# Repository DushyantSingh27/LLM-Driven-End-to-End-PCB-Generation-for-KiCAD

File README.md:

# LLM-Driven End-to-End PCB Generation for KiCad

Turn a natural-language circuit description into an **ERC-clean KiCad 9 schematic** and a **DRC-checked, routed PCB** — headless, no GUI step anywhere in the flow.

Design intent is guided by STMicroelectronics hardware design guidelines, with mentorship from ST engineers on layout practice. Manufacturability limits come from a fabricator's DFM specification. KiCad is treated as the single source of truth for every file format, and KiCad's own ERC and DRC verify the output independently of the code that produced it.

```
"STM32L476 talking to an LSM6DSM over SPI"
        │
        ├─ RAG (datasheets) + KiCad symbol resolver   →  authoritative pin table
        ├─ LLM                                        →  SKiDL (Python)
        ├─ SKiDL + ERC                                →  verified netlist
        ├─ placement + ST-style power wiring          →  native .kicad_sch
        ├─ footprints, rules, stitching, pours        →  .kicad_pcb
        ├─ Freerouting (DSN → SES)                    →  routed board
        └─ DRC + independent verifier                 →  report.json, exit 0 or 1
```

**Repo:** `https://github.com/DushyantSingh27/LLM-Driven-End-to-End-PCB-Generation-for-KiCAD`

---

## Table of contents

1. [What you get](#1-what-you-get)
2. [Requirements](#2-requirements)
3. [Install](#3-install)
4. [Configure](#4-configure--paths-you-must-change)
5. [Run the benchmark](#5-run-the-benchmark)
6. [Reading the output](#6-reading-the-output)
7. [Generating **your own** circuit](#7-generating-your-own-circuit)
8. [Troubleshooting](#8-troubleshooting)
9. [Known limits](#9-known-limits)
10. [Verified environment](#10-verified-environment)

---

## 1. What you get

The architecture rests on one separation, held throughout: **the language model decides what the circuit is; deterministic code decides what the files are.** The LLM never emits a coordinate, a trace width or a clearance. Conversely, no rule engine guesses which pin is a power pin — that comes from the netlist's own pin semantics.

Running the benchmark end-to-end reproduces this, on an STM32L476JGYxP (WLCSP-72) + LSM6DSM (LGA-14) SPI board:

| Result | Value |
|---|---|
| Components / nets / pads | 22 / 68 / 126 |
| ERC errors | **0** |
| Independent verifier | clean |
| Pads bound to nets | 126 / 126 |
| Courtyard violations | 0 |
| Copper clearance violations | **0** |
| Traces / vias after routing | 94 / 44 |
| Unconnected items | 10 *(see [§9](#9-known-limits) — this is a deliberate trade)* |
| Exit code | `1` (`INCOMPLETE`) |

### Phase 1 output — the generated schematic

Native `.kicad_sch`, opened directly in Eeschema. Power rails auto-wired in ST's drawing style: T-junctions where the stacks fit, net labels where the pin column is crowded.

### Phase 2 output — placement and routing

Constructive placement from real ball coordinates, then a force-directed legaliser; routed by Freerouting through the DSN/SES bridge.

The pipeline **reports failure honestly**. Exit code `0` means DRC-clean; `1` means something is unresolved and the report says exactly what. Do not treat a non-zero exit as "the tool is broken" — read `report.json`.

---

## 2. Requirements

| | |
|---|---|
| **OS** | Windows 10/11 with **WSL2** (Ubuntu 22.04). The split is required — see below. |
| **Python** | 3.10 (in WSL) — *and* KiCad's own bundled `python.exe` (on Windows) |
| **KiCad** | **9.0.8** on the Windows side |
| **Java** | A JRE on the Windows side, for Freerouting |
| **Freerouting** | `freerouting.jar` |
| **API key** | Anthropic, and/or NVIDIA NIM (has a free tier) |
| **Disk** | ~2 GB (Chroma index + sentence-transformers model) |

### Why two operating systems?

`pcbnew` is a SWIG binding into KiCad's C++ core. It **must** run under the same interpreter KiCad ships with. `pip install`-ing it into a Linux venv gives ABI mismatches that fail in confusing ways — segfaults, or worse, silently wrong numbers.

**The rule:**

- Anything that is **pure logic** (SKiDL, RAG, resolver, netlist parsing, schematic emit) → **WSL Python**
- Anything that **touches a board object** (placement, rules, zones, DSN/SES, DRC) → **KiCad's Windows `python.exe`**

Paths cross with `wslpath -w` going out, and `/mnt/c/...` coming back.

---

## 3. Install

### 3.1 WSL and Python

```bash
# From Windows PowerShell (once):
wsl --install -d Ubuntu-22.04
```

```bash
# Then, inside WSL:
sudo apt update
sudo apt install -y python3.10 python3.10-venv python3-pip git

cd ~
git clone https://github.com/DushyantSingh27/LLM-Driven-End-to-End-PCB-Generation-for-KiCAD.git LLM_Driven_Schematic_Gen
cd LLM_Driven_Schematic_Gen

python3 -m venv venv
source venv/bin/activate
python -V          # must print Python 3.10.x
```

> **The clone directory name matters.** Several scripts hardcode `~/LLM_Driven_Schematic_Gen`. Clone into exactly that name, or edit the paths in [§4](#4-configure--paths-you-must-change).

### 3.2 Python dependencies

```bash
pip install skidl==2.2.3
pip install anthropic==0.115.1
pip install openai==2.46.0
pip install pymupdf4llm==1.28.0 pymupdf-layout==1.28.0
pip install chromadb==1.5.9
pip install sentence-transformers==5.6.0
```

> **Do not substitute plain PyMuPDF for `pymupdf4llm`.** Plain extraction turns the STM32 ball-assignment tables into mojibake — which is precisely the data the model most needs. The failure does not appear until three stages later, as an invalid pin name.

### 3.3 KiCad 9

Install **KiCad 9.0.8** from [kicad.org](https://www.kicad.org) (Windows installer). Then verify it from WSL:

```bash
ls "/mnt/c/Program Files/KiCad/9.0/share/kicad/symbols/" | head
"/mnt/c/Program Files/KiCad/9.0/bin/python.exe" -c "import pcbnew; print(pcbnew.GetBuildVersion())"
# expect: 9.0.8
```

> ⚠️ **The install path contains a space.** Quote it *everywhere*. Unquoted, it fails silently in about half of all shell contexts.

If your KiCad lives elsewhere, override the symbol directory:

```bash
export KICAD_SYMBOL_DIR="/mnt/c/Path/To/KiCad/9.0/share/kicad/symbols"
```

### 3.4 Freerouting and Java

Install a JRE on the **Windows** side and place the jar somewhere stable, e.g. `C:\tools\freerouting\freerouting.jar`.

```bash
java -version    # confirm the JRE is reachable
```

`rag/routing.py` performs java/jar discovery and drives it headless:

```
java -jar freerouting.jar -de board.dsn -do board.ses
```

> Check which JRE version your Freerouting build requires. Recent releases track new JREs and fail on older ones with an error that does not mention Java.

### 3.5 API keys

```bash
export ANTHROPIC_API_KEY=sk-ant-...      # console.anthropic.com
export NVIDIA_API_KEY=nvapi-...          # build.nvidia.com  (only if PROVIDER="nvidia")
```

Add them to `~/.bashrc` so they survive a new shell.

> **A Claude Pro subscription is not API access.** The API bills separately.

---

## 4. Configure — paths you must change

These are hardcoded. Change them, or match them.

| File | Constant | Default | Action |
|---|---|---|---|
| `rag/pipeline.py` | `DEFAULT_OUTPUT_ROOT` | `/mnt/c/Users/Dushyant/Desktop/pcbgen_outputs` | **Must change** — or always pass `--output-root` |
| `rag/build_rag_v2.py` | `DATASHEET_DIR` | `~/LLM_Driven_Schematic_Gen/datasheets` | OK if you cloned to that name |
| `rag/build_rag_v2.py` | `CHROMA_DIR` | `~/LLM_Driven_Schematic_Gen/rag/chroma_db` | OK if you cloned to that name |
| `rag/build_rag_v2.py` | `COLLECTION` | `st_datasheets_v2` | Leave alone unless you keep multiple corpora |
| `rag/generate_spi_v2.py` | `PROVIDER` | `"anthropic"` | Set to the provider whose key you have |
| `rag/generate_spi_v2.py` | `MODEL` | `claude-sonnet-4-6` | Change to switch Anthropic model |
| `rag/generate_spi_v2.py` | `NVIDIA_MODEL` | `z-ai/glm-5.2` | Used when `PROVIDER` is NVIDIA |
| `rag/generate_spi_v2.py` | `OUTPUT_PY` | `rag/lsm6dsm_stm32l476_spi_v2.py` | Where the generated SKiDL is written |
| *(env)* | `KICAD_SYMBOL_DIR` | KiCad 9 default path | Set only if KiCad is installed elsewhere |

The output root must be a **Windows-visible** path (under `/mnt/c/...`), because Phase 2 runs under Windows Python and has to read what Phase 1 wrote.

---

## 5. Run the benchmark

### Step 1 — Build the RAG index *(once per datasheet set)*

Put component datasheet PDFs in `datasheets/`. The filename becomes the component key:

```
datasheets/STM32L476.pdf   →  component "STM32L476"
datasheets/LSM6DSM.pdf     →  component "LSM6DSM"
```

```bash
source ~/LLM_Driven_Schematic_Gen/venv/bin/activate
cd ~/LLM_Driven_Schematic_Gen/rag
python build_rag_v2.py
```

Extracts with `pymupdf4llm` (layout-aware markdown), splits on `#`/`##`/`###`, chunks at 1200 chars with 120 overlap, embeds, and writes a persistent Chroma collection to `rag/chroma_db`.

### Step 2 — Phase 1: prompt → verified schematic

```bash
python pipeline.py --name spi_auto --output-root /mnt/c/Users/<YOU>/Desktop/pcbgen_outputs
```

One command. It runs generation (LLM → SKiDL → ERC), then the serialiser (netlist → placement → ST-style power wiring → `.kicad_sch`), then verification.

```bash
# Re-run the serialiser on the last generated netlist, without paying for tokens:
python pipeline.py --name spi_auto --skip-generate
```

`--skip-generate` is the flag you will use most. Use it whenever you are debugging the serialiser rather than the model.

### Step 3 — Phase 2: netlist → routed board

Launch this with **KiCad's Windows Python**, not the venv:

```bash
RUN=/mnt/c/Users/<YOU>/Desktop/pcbgen_outputs/spi_auto

"/mnt/c/Program Files/KiCad/9.0/bin/python.exe" \
  "$(wslpath -w ~/LLM_Driven_Schematic_Gen/rag/layout_pipeline.py)" \
  "$(wslpath -w $RUN/spi_auto.net)" \
  "$(wslpath -w $RUN)"

echo "exit code: $?"     # 0 = DRC clean, 1 = incomplete
```

`layout_pipeline.py` takes exactly **two positional arguments**: the netlist path and the output directory. Both must be **Windows-style** paths.

---

## 6. Reading the output

`run_context.py` gives every run its own directory with structural uniqueness:

| Artifact | What it is |
|---|---|
| `board.kicad_pcb` | The board — open it in pcbnew |
| `board.dsn` | What was handed to the router |
| `board.ses` | What the router handed back |
| `drc.rpt` | KiCad's own DRC report |
| `router.log` | Freerouting's output, parsed for the unrouted count |
| `report.json` | **Start here.** Stage-by-stage results, not just a verdict. |

The console log is stage-numbered (`[L1/12] … [L12/12]`) and names anything it could not do rather than dropping it silently — e.g. `UNREACHABLE U1 pad H8 (/VDD_3V3)`.

---

## 7. Generating your own circuit

The benchmark is not special. To generate a different board:

### 7.1 Add the datasheets

```bash
cp MY_MCU.pdf MY_SENSOR.pdf ~/LLM_Driven_Schematic_Gen/datasheets/
cd ~/LLM_Driven_Schematic_Gen/rag
python build_rag_v2.py        # rebuild the index
```

### 7.2 Edit the spec in `rag/generate_spi_v2.py`

Three constants define the circuit:

```python
USER_TASK  = "..."     # the natural-language spec, e.g. "connect X to Y over I2C
                       #  with pull-ups, decouple every supply rail"
COMPONENTS = {...}     # part number → KiCad symbol/library mapping
RAG_QUERIES = [...]    # what to retrieve from the datasheets before prompting
```

`RAG_QUERIES` is the one people under-invest in. The model is only as grounded as what you retrieve. For a new part, query for the **ball/pin assignment table**, the **supply rail list**, and the **decoupling recommendations** at minimum.

There are worked examples in the repo for other topologies: `generate_i2c_circuit.py`, `generate_st_circuit.py`.

### 7.3 Run it

```bash
python pipeline.py --name my_board --output-root /mnt/c/Users/<YOU>/Desktop/pcbgen_outputs
```

then Phase 2 as in [§5 step 3](#step-3--phase-2-netlist--routed-board).

### 7.4 Expect to hit the generalisation gaps

Be aware before you start (details in [§9](#9-known-limits)):

- The placer contains **circuit-specific reference designators**. A different topology can trip them.
- Net names must match the pipeline's **contract** (`GND`, `VDD_3V3`, `VREF_PLUS`, …). A model that emits `VSS` or `VREF+` will break the power-wiring stage.
- Only **single-sided** placement is supported.

---

## 8. Troubleshooting

**`ImportError: No module named pcbnew`**
You ran Phase 2 with the venv Python. Use KiCad's `python.exe`.

**Design rules look wrong / clearance numbers don't match what you set**
KiCad 9 stores netclass **definitions** in the `.kicad_pro` project file, not the `.kicad_pcb`, and `SaveBoard` will not overwrite an existing project file. A stale `.kicad_pro` silently overrides your computed rules and invalidates every measurement taken afterwards. `save_board` clears them — but if you are writing your own stage, delete the project file before saving.

**Python exits with no traceback during the pour stage**
`ZONE_FILLER` hard-crashes at the C++ level on an in-memory board. `BuildConnectivity()` does not help. There is a deliberate **save/reload seam** before pouring; do not remove it.

**Netclasses vanish after a save/reload**
Expected — the definitions live in the project file. This is why DSN clearance inflation is done **in memory** and reverted immediately, rather than via a round-trip.

**A shell command "does nothing"**
You did not quote `"/mnt/c/Program Files/KiCad/9.0/..."`.

**The router succeeds but KiCad's DRC rejects the board**
DSN carries copper-to-copper clearance; it does **not** carry KiCad's hole-to-copper rule. The exported clearance is inflated so one implies the other:

```
c_router = max(c_copper, c_hole + r_hole − r_via) = 0.1250 mm
```

**Invalid pin names in the generated SKiDL**
Your RAG index is probably built from mangled extraction. Confirm `pymupdf4llm` is installed (not plain PyMuPDF) and rebuild.

---

## 9. Known limits

Stated plainly, because a pipeline that oversells itself moves error discovery to the fab.

**10 unconnected items — a measured trade, not a bug.**
All ten are WLCSP-72 inner-ball escape routes. At 0.4 mm ball pitch the keep-out ring leaves no legal channel for a through-via to reach U1's inner balls. The clearance choice was measured, not guessed:

| Router clearance | Unrouted | Hole violations |
|---|---|---|
| 0.09 mm | 6 | **14** |
| **0.1250 mm** | **10** | **0** |

The 0.09 mm board connects four more nets and is **not manufacturable**. The pipeline takes the manufacturable board. Closing the remaining ten is a *stackup* decision — microvias or more layers — not a router tuning problem.

**No intentional trace widths.** `m_TrackMinWidth` is a DRC minimum, not the width the router uses. Netclasses with real per-class widths are not implemented yet, so trace widths are the DSN default.

**Single-sided placement only.** The placer has no concept of a bottom side.

**Circuit-specific hardcodes in placement.** Some reference designators are baked in.

**No generation-contract normalisation.** `VSS`/`GND`, `VDD`/`VDD_3V3`, `VREF+`/`VREF_PLUS`, `100n`/`100nF` are not yet unified.

**Silkscreen placement not implemented.** 10 silkscreen warnings are deferred; they are cosmetic.

**LLM stage is not reproducible on Anthropic.** No seed is exposed. NVIDIA NIM does expose one.

**Freerouting is heuristic.** Runs may route differently; the DRC verdict has been stable in practice.

---

## 10. Verified environment

This exact combination is what the results above were produced on.

| Component | Version |
|---|---|
| KiCad / `pcbnew` | **9.0.8** |
| OS | Ubuntu 22.04 (WSL2) |
| Python | 3.10 |
| `skidl` | 2.2.3 |
| `anthropic` | 0.115.1 |
| `openai` | 2.46.0 |
| `pymupdf` | 1.28.0 |
| `pymupdf-layout` | 1.28.0 |
| `pymupdf4llm` | 1.28.0 |
| `chromadb` | 1.5.9 |
| `sentence-transformers` | 5.6.0 |

**Not yet pinned** — record these yourself, they silently change results:
Freerouting jar version · JRE version · fab DFM spec revision.

`pcbnew` is a binding to a *specific* KiCad build. A minor version bump can change enum names, default clearances, or whether a call exists — and the failure shows up as a wrong **number**, not an exception. Pin it.

---

## Design principle

> **The language model decides what the circuit is. Deterministic code decides what the files are.**

The LLM never emits a coordinate, a trace width or a clearance. No model output reaches a file without passing a machine check, and there are always **two independent judges** — the authoritative tool (ERC, DRC) *and* an independent verifier that reads geometry rather than intent. Neither is trusted alone.

A disappearing ERC error is worse news than a new one: it means two nets silently merged, and the check that would have complained is now satisfied by the short itself.

---

## Acknowledgements

Built by **Dushyant Singh**, mentored by **Saurabh Rawat**, STMicroelectronics.

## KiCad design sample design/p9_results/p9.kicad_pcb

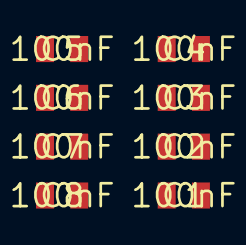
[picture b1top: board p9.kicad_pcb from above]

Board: 2 copper layers, 8 parts (0 on the bottom side), 2 nets, no tracks yet.

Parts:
C1, C2, C3, C4, C5, C6, C7, C8: 100nF; C_0805

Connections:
PGND: C1.2, C2.2, C3.2, C4.2, C5.2, C6.2, C7.2, C8.2
VBUS+: C1.1, C2.1, C3.1, C4.1, C5.1, C6.1, C7.1, C8.1

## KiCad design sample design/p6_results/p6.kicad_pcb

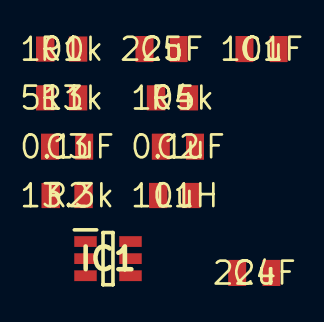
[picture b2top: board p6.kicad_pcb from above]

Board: 2 copper layers, 11 parts (0 on the bottom side), 7 nets, no tracks yet.

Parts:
C1: 10uF; C_0805
C2, C3: 0.1uF; C_0805
C4, C5: 22uF; C_0805
IC1: TPS54302
L1: 10uH; L_0805
R1: 100k; R_0805
R2: 13.3k; R_0805
R3: 511k; R_0805
R4: 105k; R_0805

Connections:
BOOT: C3.1, IC1.6
EN: IC1.5, R3.2, R4.1
FB: IC1.4, R1.2, R2.1
GND: C1.2, C2.2, C4.2, C5.2, IC1.1, R2.2, R4.2
SW: C3.2, IC1.2, L1.1
VIN: C1.1, C2.1, IC1.3, R3.1
VOUT: C4.1, C5.1, L1.2, R1.1

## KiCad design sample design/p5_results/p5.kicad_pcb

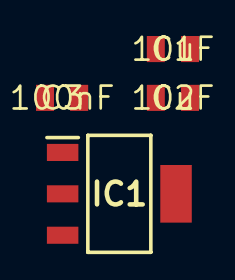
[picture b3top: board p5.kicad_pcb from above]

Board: 2 copper layers, 4 parts (0 on the bottom side), 3 nets, no tracks yet.

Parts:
C1, C2: 10uF; C_0805
C3: 100nF; C_0805
IC1: TLV1117-33

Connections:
GND: C1.2, C2.2, C3.2, IC1.1
VIN: C1.1, IC1.3
VOUT: C2.1, C3.1, IC1.2, IC1.4

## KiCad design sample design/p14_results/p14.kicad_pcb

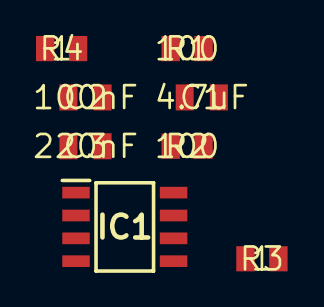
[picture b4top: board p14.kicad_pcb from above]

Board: 2 copper layers, 8 parts (0 on the bottom side), 8 nets, no tracks yet.

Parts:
C1: 4.7uF; C_0805
C2: 100nF; C_0805
C3: 220nF; C_0805
IC1: UCC27211
R1, R2: 100; R_0805
R3, R4: 1; R_0805

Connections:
unnamed: IC1.5, R1.2
unnamed: IC1.6, R2.2
unnamed: IC1.3, R3.1
unnamed: IC1.8, R4.1
PGND: C1.2, C2.2, IC1.7
VB: C3.1, IC1.2
VCC: C1.1, C2.1, IC1.1
VS: C3.2, IC1.4

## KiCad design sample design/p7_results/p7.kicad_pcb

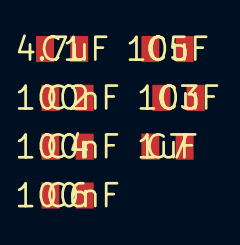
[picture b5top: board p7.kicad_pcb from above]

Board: 2 copper layers, 7 parts (0 on the bottom side), 5 nets, no tracks yet.

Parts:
C1: 4.7uF; C_0805
C2, C4, C6: 100nF; C_0805
C3, C5: 10uF; C_0805
C7: 1uF; C_0805

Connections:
ISO_0V: C3.2, C4.2, C5.1, C6.1
PGND: C1.2, C2.2
VIN: C1.1, C2.1
VISO+: C3.1, C4.1, C7.1
VISO-: C5.2, C6.2, C7.2

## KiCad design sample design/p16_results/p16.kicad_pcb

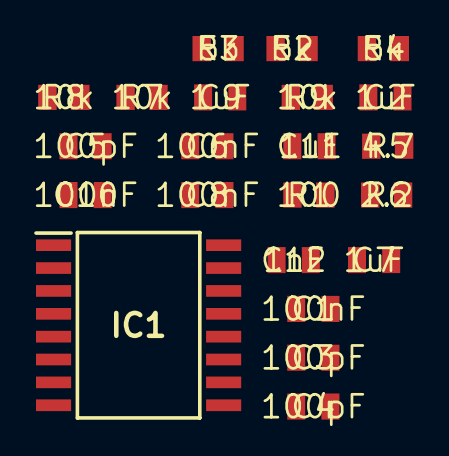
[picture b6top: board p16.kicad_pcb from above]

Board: 2 copper layers, 22 parts (0 on the bottom side), 15 nets, no tracks yet.

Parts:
C1, C6, C8, C10: 100nF; C_0805
C2, C7, C9, C11: 1uF; C_0805
C3, C4, C5: 100pF; C_0805
C12: 1nF; C_0805
IC1: UCC21710
R1: 100; R_0805
R2, R3, R4: 5k; R_0805
R5: 4.7; R_0805
R6: 2.2; R_0805
R7, R8, R9: 10k; R_0805

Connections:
COM: C6.2, C7.2, C8.1, C9.1, C12.2, IC1.3, R9.2
DESAT_DIV: R7.2, R8.1
FLT: C3.1, IC1.13, R2.2
GATE: IC1.7, R5.2, R6.2
GND: C1.2, C2.2, C3.2, C4.2, C5.2, IC1.9, IC1.11
unnamed: IC1.10, R1.2
unnamed: IC1.4, R5.1
unnamed: IC1.6, R6.1
OC_NODE: C12.1, IC1.2, R8.2, R9.1
RDY: C4.1, IC1.12, R3.2
RST_EN: C5.1, IC1.14, R4.2
VCC: C1.1, C2.1, IC1.15, R2.1, R3.1, R4.1
VDD: C6.1, C7.1, C10.1, C11.1, IC1.5, R7.1
VEE: C8.2, C9.2, C10.2, C11.2, IC1.8
__NOCONNECT: IC1.1, IC1.16

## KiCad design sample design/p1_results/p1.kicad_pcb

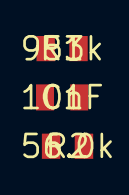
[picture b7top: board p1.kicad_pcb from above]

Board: 2 copper layers, 3 parts (0 on the bottom side), 2 nets, no tracks yet.

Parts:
C1: 10nF; C_0805
R1: 953k; R_0805
R2: 56.0k; R_0805

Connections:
GND: C1.2, R2.2
VSENSE: C1.1, R1.2, R2.1

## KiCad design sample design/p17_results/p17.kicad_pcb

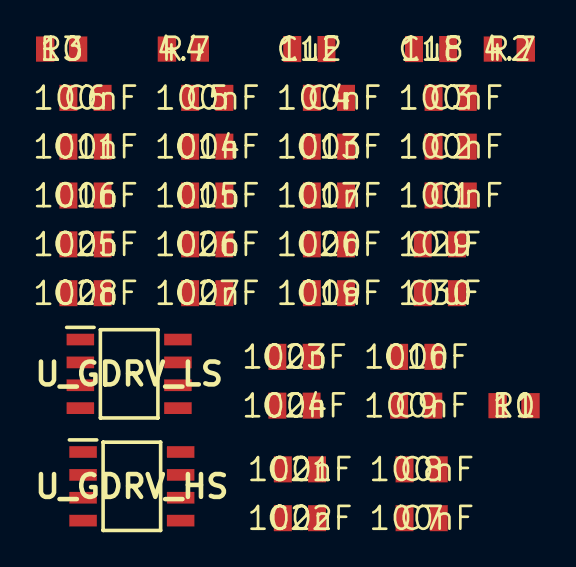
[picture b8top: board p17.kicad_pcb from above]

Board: 2 copper layers, 36 parts (0 on the bottom side), 15 nets, no tracks yet.

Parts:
C1, C2, C3, C4, C5, C6, C7, C8, C9, C10, C11, C13, C14, C15, C16, C17, C19, C20, C21, C22, C23, C24, C25, C26, C27, C28: 100nF; C_0805
C12, C18: 1uF; C_0805
C29, C30: 10uF; C_0805
R1, R3: 10; R_0805
R2, R4: 4.7; R_0805
U_GDRV_HS: UCC5390E
U_GDRV_LS: UCC5390E

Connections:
COM_HS: C10.2, C11.1, C14.2, U_GDRV_HS.7
COM_LS: C16.2, C17.1, C20.2, U_GDRV_LS.7
GATE_H: R1.2, R2.2
GATE_L: R3.2, R4.2
GDRV_OUT_H: R1.1, U_GDRV_HS.6
GDRV_OUT_L: R3.1, U_GDRV_LS.6
GND_PRI: C9.2, C13.2, C15.2, C19.2, U_GDRV_HS.3, U_GDRV_HS.4, U_GDRV_LS.3, U_GDRV_LS.4
PGND: C1.2, C2.2, C3.2, C4.2, C5.2, C6.2, C7.2, C8.2, C21.2, C22.2, C23.2, C24.2, C25.2, C26.2, C27.2, C28.2, C29.2, C30.2
VBUS: C1.1, C2.1, C3.1, C4.1, C5.1, C6.1, C7.1, C8.1
VCC_PRI: C9.1, C13.1, C15.1, C19.1, U_GDRV_HS.1, U_GDRV_LS.1
VDD_HS: C10.1, C12.1, C14.1, U_GDRV_HS.5
VDD_LS: C16.1, C18.1, C20.1, U_GDRV_LS.5
VEE_HS: C11.2, C12.2, U_GDRV_HS.8
VEE_LS: C17.2, C18.2, U_GDRV_LS.8
VOUT: C21.1, C22.1, C23.1, C24.1, C25.1, C26.1, C27.1, C28.1, C29.1, C30.1
